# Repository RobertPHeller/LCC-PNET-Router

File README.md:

# LCC-PNET-Router

This is a "router" between a LCC network and a Pricom Lighting PNET network.
It translates between LCC event reports and PNET Trigger, Control, and Dimmer 
messages.  The PCB contains CAN transceivers for the two CAN IFs on a 
PocketBeagle, with one wired to LCC network connectors (RJ45s) and the other 
wired for PNET (RJ12 6-6).  The "firmware" compiles and runs on a 32-bit ARM
Linux SBC (tested on a Beagle Bone using GridConnect over Tcp/Ip for the LCC
network and the Virtual CAN driver (vcan) for the PNET network.

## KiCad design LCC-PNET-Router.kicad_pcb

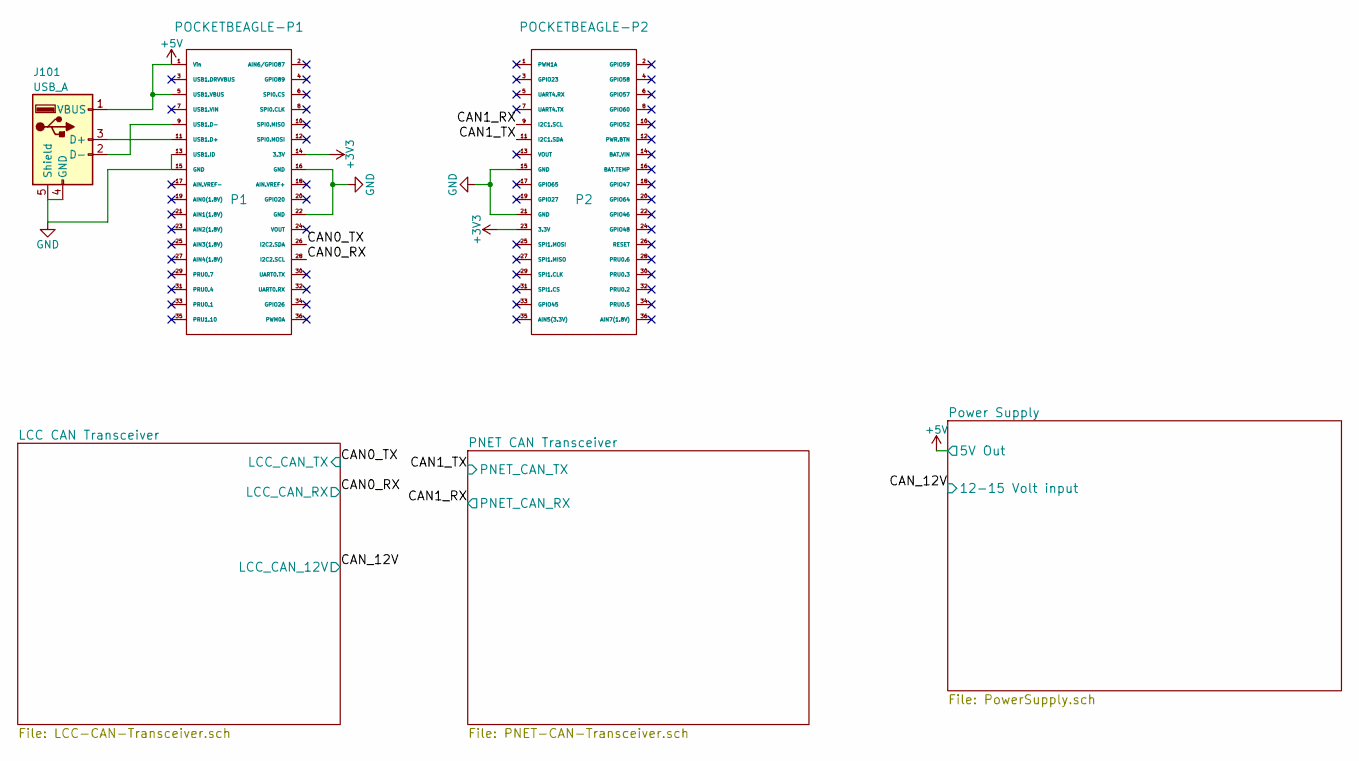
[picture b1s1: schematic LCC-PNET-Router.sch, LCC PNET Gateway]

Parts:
J101: USB_A; USB-A-UPRIGHT; Mouser Part Number 710-614004184726
P1: POCKETBEAGLE-P1; Socket_Strip_Straight_2x18_Pitch2.54mm; Mouser Part Number 517-929975-01-18-RK
P2: POCKETBEAGLE-P2; Socket_Strip_Straight_2x18_Pitch2.54mm; Mouser Part Number 517-929975-01-18-RK

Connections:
+5V: J101.1 (VBUS), P1.1 (Vin), P1.5 (USB1.VBUS); also elsewhere on the board
/CAN0_RX: P1.28 (I2C2.SCL); also elsewhere on the board
/CAN0_TX: P1.26 (I2C2.SDA); also elsewhere on the board
/CAN1_RX: P2.9 (I2C1.SCL); also elsewhere on the board
/CAN1_TX: P2.11 (I2C1.SDA); also elsewhere on the board
GND: J101.4 (GND), J101.5 (Shield), P1.13 (USB1.ID), P1.15 (GND), P1.16 (GND), P1.22 (GND), P2.15 (GND), P2.21 (GND); also elsewhere on the board
unnamed: J101.2 (D-), P1.9 (USB1.D-)
unnamed: J101.3 (D+), P1.11 (USB1.D+)

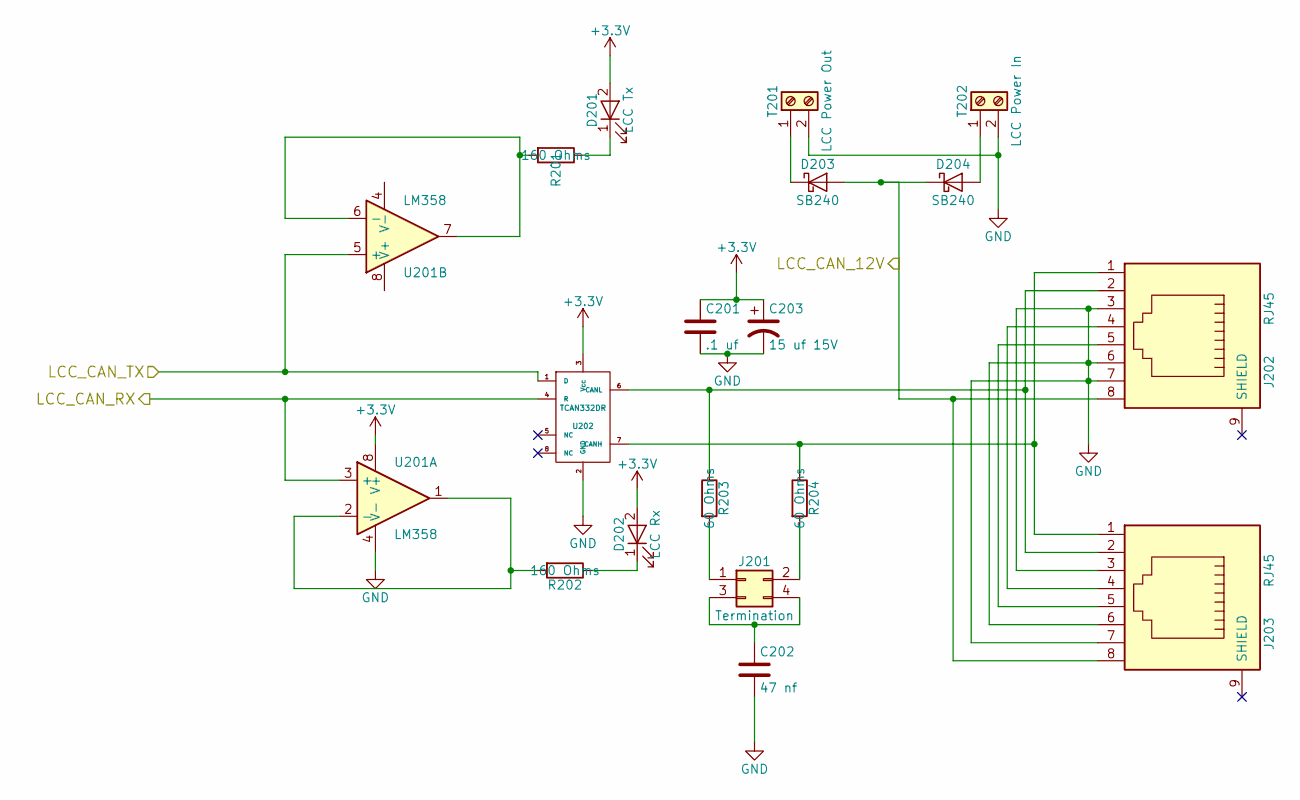
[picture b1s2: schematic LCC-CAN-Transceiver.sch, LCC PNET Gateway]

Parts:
C201: .1 uf; C_0603; Mouser Part Number 603-CC603KPX7R9BB104
C202: 47 nf; C_0603; Mouser Part Number 963-GMK107BJ473KAHT
C203: 15 uf 15V; CP_Elec_4x5.8; Mouser Part Number 647-UUD1C150MCL
D201: LCC Tx; LED_0603; Mouser Part Number 710-150060SS75000
D202: LCC Rx; LED_0603; Mouser Part Number 710-150060YS75000
D203, D204: SB240; D_PowerDI-123; Mouser Part Number 621-DFLS240-7
J201: Termination; Pin_Header_Straight_2x02_Pitch2.54mm; Mouser Part Number 649-1012938190402BLF
J202, J203: RJ45; RJ45_8N-S; Mouser Part Number 710-615008144221
R201, R202: 160 Ohms; R_0603; Mouser Part Number 603-AC0603JR-07160RL
R203, R204: 60 Ohms; R_1206; Mouser Part Number 71-CRCW120660R0KNAIF
T201: LCC Power Out; TerminalBlock_Pheonix_MPT-2.54mm_2pol; Mouser Part Number 651-1725656
T202: LCC Power In; TerminalBlock_Pheonix_MPT-2.54mm_2pol; Mouser Part Number 651-1725656
U201: LM358; SOIC-8_3.9x4.9mm_Pitch1.27mm; Mouser Part Number 595-LM358DR
U202: TCAN332DR; SOIC-8_3.9x4.9mm_Pitch1.27mm; Mouser Part Number 595-TCAN332DR

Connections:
/CAN0_RX: U201.3 (+), U202.4 (R); also elsewhere on the board
/CAN0_TX: U201.5 (+), U202.1 (D); also elsewhere on the board
/CAN_12V: D203.2 (A), D204.1 (K), J202.8, J203.8; also elsewhere on the board
GND: C201.2, C202.2, C203.2, J202.3, J202.6, J202.7, J203.3, J203.6, J203.7, T201.2, T202.2, U201.4 (V-), U202.2 (GND); also elsewhere on the board
unnamed: C202.1, J201.3, J201.4
unnamed: D201.1 (K), R201.1
unnamed: D202.1 (K), R202.1
unnamed: D203.1 (K), T201.1
unnamed: D204.2 (A), T202.1
unnamed: J201.1, R203.2
unnamed: J201.2, R204.2
unnamed: J202.1, J203.1, R204.1, U202.7 (CANH)
unnamed: J202.2, J203.2, R203.1, U202.6 (CANL)
unnamed: J202.4, J203.4
unnamed: J202.5, J203.5
unnamed: R201.2, U201.6 (-), U201.7
unnamed: R202.2, U201.1, U201.2 (-)

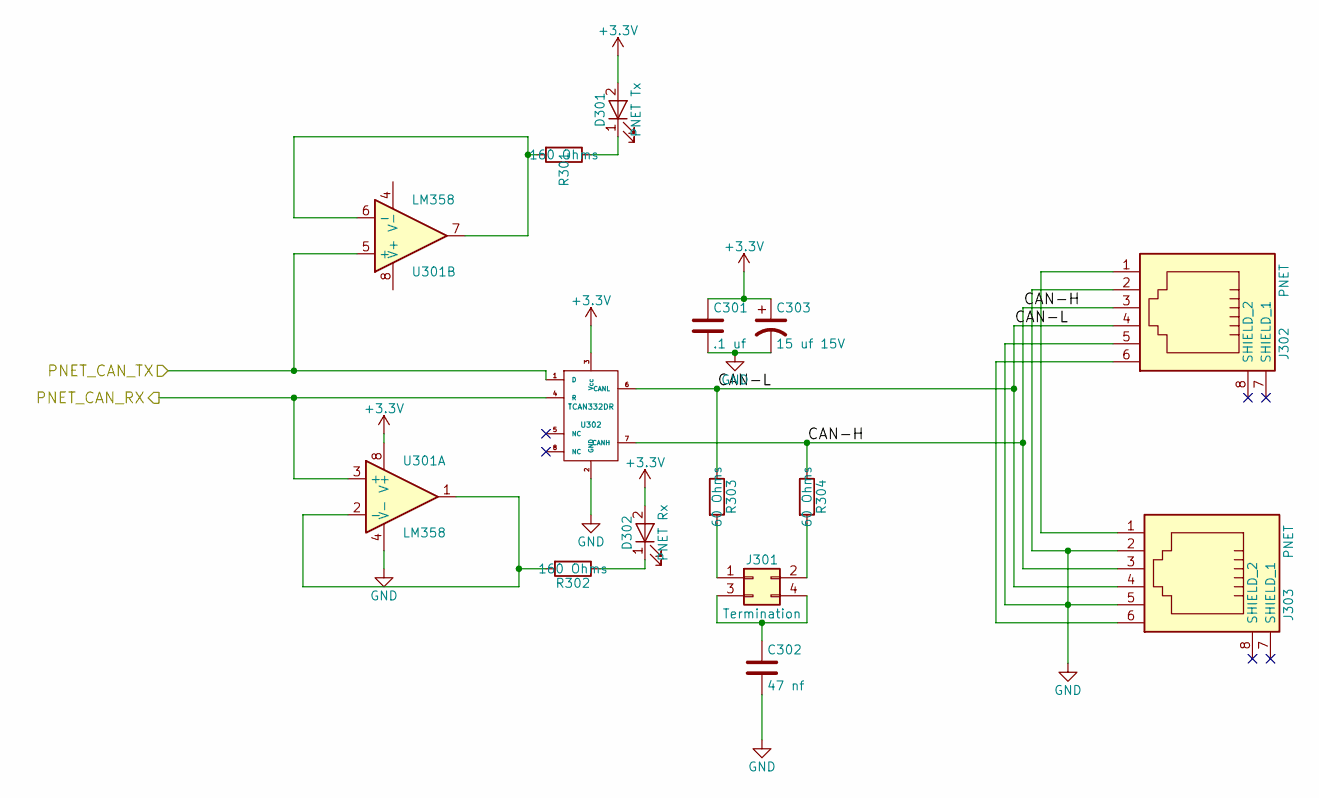
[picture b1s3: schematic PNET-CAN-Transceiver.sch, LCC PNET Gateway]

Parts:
C301: .1 uf; C_0603; Mouser Part Number 603-CC603KPX7R9BB104
C302: 47 nf; C_0603; Mouser Part Number 963-GMK107BJ473KAHT
C303: 15 uf 15V; CP_Elec_4x5.8; Mouser Part Number 647-UUD1C150MCL
D301: PNET Tx; LED_0603; Mouser Part Number 710-150060SS75000
D302: PNET Rx; LED_0603; Mouser Part Number 710-150060YS75000
J301: Termination; Pin_Header_Straight_2x02_Pitch2.54mm; Mouser Part Number 649-1012938190402BLF
J302, J303: PNET; 95501-2661; Mouser Part Number 538-95501-2661
R301, R302: 160 Ohms; R_0603; Mouser Part Number 603-AC0603JR-07160RL
R303, R304: 60 Ohms; R_1206; Mouser Part Number 71-CRCW120660R0KNAIF
U301: LM358; SOIC-8_3.9x4.9mm_Pitch1.27mm; Mouser Part Number 595-LM358DR
U302: TCAN332DR; SOIC-8_3.9x4.9mm_Pitch1.27mm; Mouser Part Number 595-TCAN332DR

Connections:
/CAN1_RX: U301.3 (+), U302.4 (R); also elsewhere on the board
/CAN1_TX: U301.5 (+), U302.1 (D); also elsewhere on the board
/PNET CAN Transceiver/CAN-H: J302.3, J303.3, R304.1, U302.7 (CANH)
/PNET CAN Transceiver/CAN-L: J302.4, J303.4, R303.1, U302.6 (CANL)
GND: C301.2, C302.2, C303.2, J302.2, J302.5, J303.2, J303.5, U301.4 (V-), U302.2 (GND); also elsewhere on the board
unnamed: C302.1, J301.3, J301.4
unnamed: D301.1 (K), R301.1
unnamed: D302.1 (K), R302.1
unnamed: J301.1, R303.2
unnamed: J301.2, R304.2
unnamed: J302.1, J303.1
unnamed: J302.6, J303.6
unnamed: R301.2, U301.6 (-), U301.7
unnamed: R302.2, U301.1, U301.2 (-)

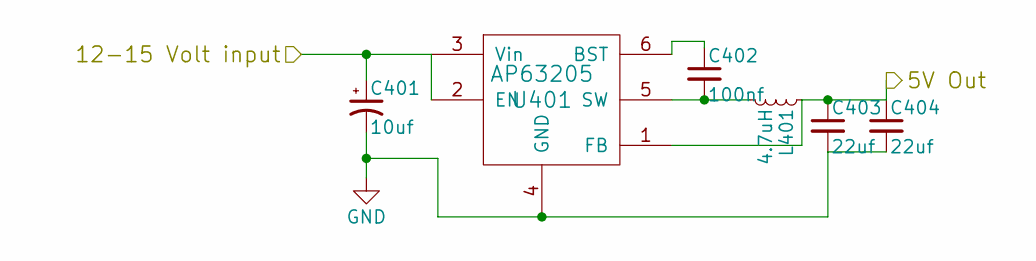
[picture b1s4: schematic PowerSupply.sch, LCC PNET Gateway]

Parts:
C401: 10uf; CP_Elec_5x5.3; Mouser Part Number 710-865230542002
C402: 100nf; C_0603; Mouser Part Number 710-885012206020
C403, C404: 22uf; C_0603; Mouser Part Number 81-GRM188R60G226ME0J
L401: 4.7uH; L_7.3x7.3_H4.5; Mouser Part Number 81-B1047AS-4R7NP3
U401: AP63205; TSOT-23-6_MK06A; Mouser Part Number 621-AP63205WU-7

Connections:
+5V: C403.1, C404.1, L401.1, U401.1 (FB); also elsewhere on the board
/CAN_12V: C401.1, U401.2 (EN), U401.3 (Vin); also elsewhere on the board
GND: C401.2, C403.2, C404.2, U401.4 (GND); also elsewhere on the board
unnamed: C402.1, U401.6 (BST)
unnamed: C402.2, L401.2, U401.5 (SW)

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
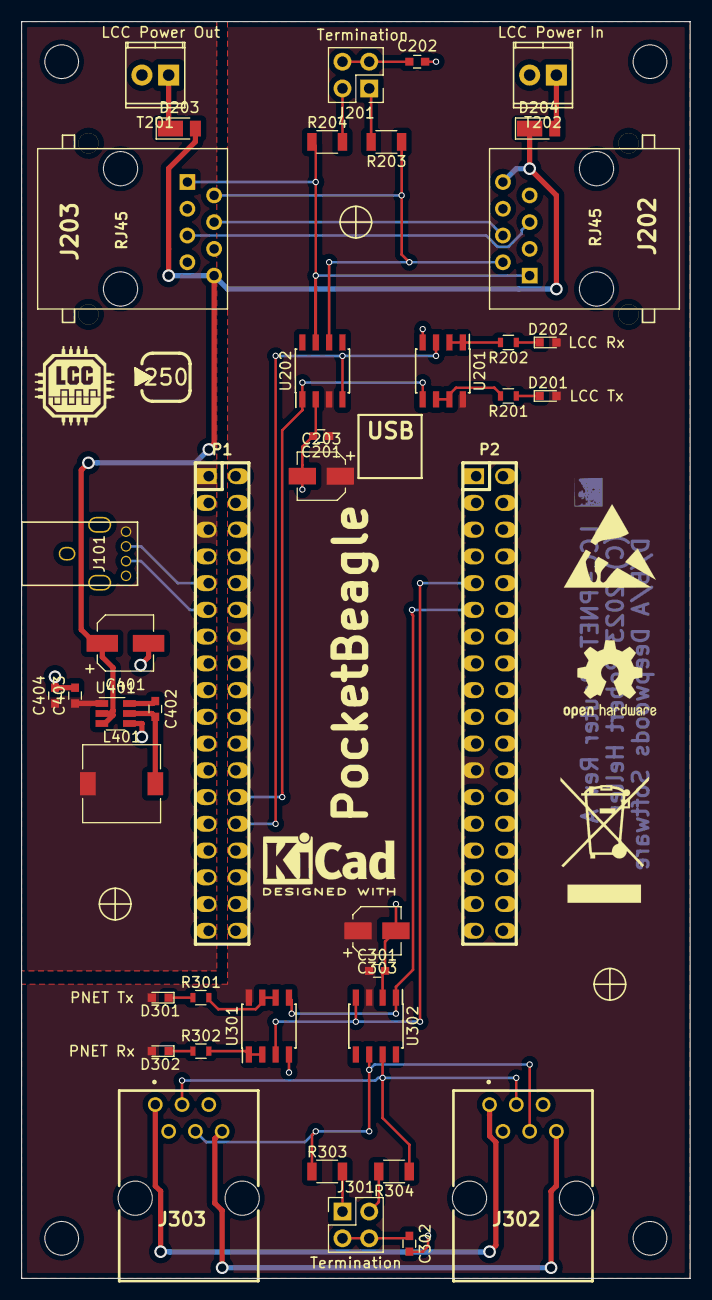
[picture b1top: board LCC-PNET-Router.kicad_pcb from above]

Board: 2 copper layers, 63.5 x 119.4 mm, 41 parts (0 on the bottom side), 36 nets.

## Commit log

2023-01-12 Start on LCC <=> PNET router.
2023-01-12 Start firmware build infrastructure.
2023-01-12 Boilerplate for the firmware done.
2023-01-12 Start on PCB layout.
2023-01-12 Update Makefile (no doc dir, at least for now).
2023-03-15 Completed initial HW design.
2023-03-15 Add Schematic PDF.
2023-03-15 Build Infrastructure, start on PNETStack.
2023-03-15 Correct for CAN Polarity on the PNET connectors.
2023-03-16 Add low-level classes.
2023-03-16 Update .gitignore.
2023-03-16 Working on PNET Can IF.
2023-03-17 Working on PNET message handlers.
2023-03-18 Complete PNETTriggerService.
2023-03-18 Refactor PNETTriggerService using an iterator flow.
2023-03-19 Working on PNET code.
2023-03-20 Completed ConfiguredPCPNetTrigger.
2023-03-20 Fix Hardware Implementation string.
2023-03-20 Add Enable flag.
2023-03-20 Start on ConfiguredPCPNetControl and ConfiguredPCPNetDimmer.
2023-03-20 Basic code completed, working on documentation.
2023-03-21 Update documentation build infrastructure.
2023-03-21 Working on documentation.
2023-03-22 Completed and tested firmware, including documentation.
2023-03-22 Add build revisions to documentation.
2023-03-22 Update RJ12 Jacks.
2023-03-22 Complete 3D and final touches on PCB.
2023-03-23 Finalize Parts Lists, generate Gerbers, etc.
2023-03-26 Add Readme.
2023-03-26 New LICENSE
2023-03-26 Add License
2023-03-29 Last minute update: dims and fids.
2023-03-30 Start on kit booklet.
2023-03-30 Add LCC-PNET-ROUTER-3D.png.
2023-03-30 Working on kit booklet pages.
2023-03-31 Add Termination Jumper Images
2023-03-31 Finish KitBooklet.
2023-03-31 Updates to startup procedures.
2023-04-02 Fix small typos.
2023-04-02 Add missing parts to Mouser BOM.
2023-04-02 Add SystemD files.
2023-05-14 Change documentation to letter sized paper.
2023-05-14 Front Cover of kit booklet.
2023-05-16 Update PCB: fix errors.
2023-06-10 Add in new kicad files.
2023-06-10 Fix minor typos in systemd files.
2023-06-14 Add ProductKit.md.
2023-06-17 Correct Config to match docs.
2023-06-17 Minor documentation update.
2023-07-02 Add Kit Insert.
2023-07-10 Add booklet insert generation.
2023-07-11 Change to use pdfbook2 v1.2 to make the kit booklet.

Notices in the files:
LCC-PNET-Router.kicad_pcb:
(C) 2023 Robert Heller
